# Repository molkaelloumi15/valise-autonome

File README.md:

# 🧳 Valise Autonome

Projet académique (2ᵉ année d'ingénieur, ENSIT, 2024–2025) réalisé en binôme (Molka Elloumi & Fakhri Menjli) : une valise connectée capable de **suivre automatiquement son propriétaire**, d'**éviter les obstacles**, et pilotable via une **application mobile Flutter**.

## 🎯 Fonctionnalités principales

| Fonctionnalité | Description |
|---|---|
| **Suivi autonome** | La valise détecte la position de son propriétaire en temps réel et le suit automatiquement. |
| **Navigation & évitement d'obstacles** | Détection et contournement des obstacles fixes et mobiles à l'aide de capteurs ultrasoniques. |
| **Mode manuel** | Contrôle manuel de la valise depuis l'application mobile. |
| **Notifications** | Alerte envoyée au smartphone en cas de perte de connexion avec la valise. |
| **Autonomie** | Batterie lithium-ion dimensionnée pour au moins 8h d'utilisation continue. |

## 🧠 Principe de fonctionnement

La valise embarque un microcontrôleur **ESP32** qui :
1. Estime la distance au smartphone du propriétaire à partir de la puissance du signal Wi-Fi (RSSI).
2. Mesure en parallèle la distance aux obstacles via un capteur ultrasonique.
3. Compare les deux mesures pour distinguer un vrai obstacle d'un simple éloignement du propriétaire, et ajuste le déplacement des moteurs en conséquence.
4. Expose ces données via un petit serveur web embarqué (mode point d'accès Wi-Fi), interrogé par l'application mobile.

## 🛠️ Stack technique

- **Firmware** : C++ (Arduino), ESP32, capteurs ultrasoniques HC-SR04, moteurs CC à engrenages FIT0564
- **Électronique** : PCB personnalisé conçu sous **KiCad**, prototypage sous **Proteus 8 ISIS**
- **Application mobile** : **Flutter** (architecture MVVM) — authentification, écran d'accueil, suivi en temps réel, réglages
- **Outils** : Arduino IDE, VS Code, KiCad

## 📂 Structure du dépôt

```
.
├── firmware/           # Code embarqué ESP32 (Arduino)
│   └── valise_autonome.ino
├── circuit/             # Conception électronique (KiCad)
│   ├── circuit.kicad_sch / .kicad_pcb / .kicad_pro
│   └── gerbers/          # Fichiers de fabrication (Gerber/drill)
├── mobile-app/          # Application Flutter (code source Dart)
│   ├── lib/
│   │   ├── main.dart
│   │   ├── screens/      # Login, Home, Profil, Réglages
│   │   └── services/     # Authentification, communication ESP32
│   ├── assets/
│   └── pubspec.yaml
└── docs/
    └── Valise_autonome.pdf   # Rapport de projet complet
```

## 📄 Documentation complète

Le rapport de projet complet (cahier des charges, étude de l'existant, architecture, choix techniques, résultats de tests) est disponible dans [`docs/Valise_autonome.pdf`](docs/Valise_autonome.pdf).

## 🚀 Pour reproduire le firmware

1. Ouvrir `firmware/valise_autonome.ino` dans l'Arduino IDE avec le support ESP32 installé.
2. Flasher la carte ESP32.
3. Se connecter au réseau Wi-Fi `Suitcase_AP` créé par la valise.
4. Lancer l'application Flutter (`mobile-app/`) pour piloter et suivre la valise.

---

*Projet réalisé dans le cadre de la formation d'ingénieur à l'ENSEA — Molka Elloumi, [LinkedIn](https://linkedin.com/in/molkaelloumi)*

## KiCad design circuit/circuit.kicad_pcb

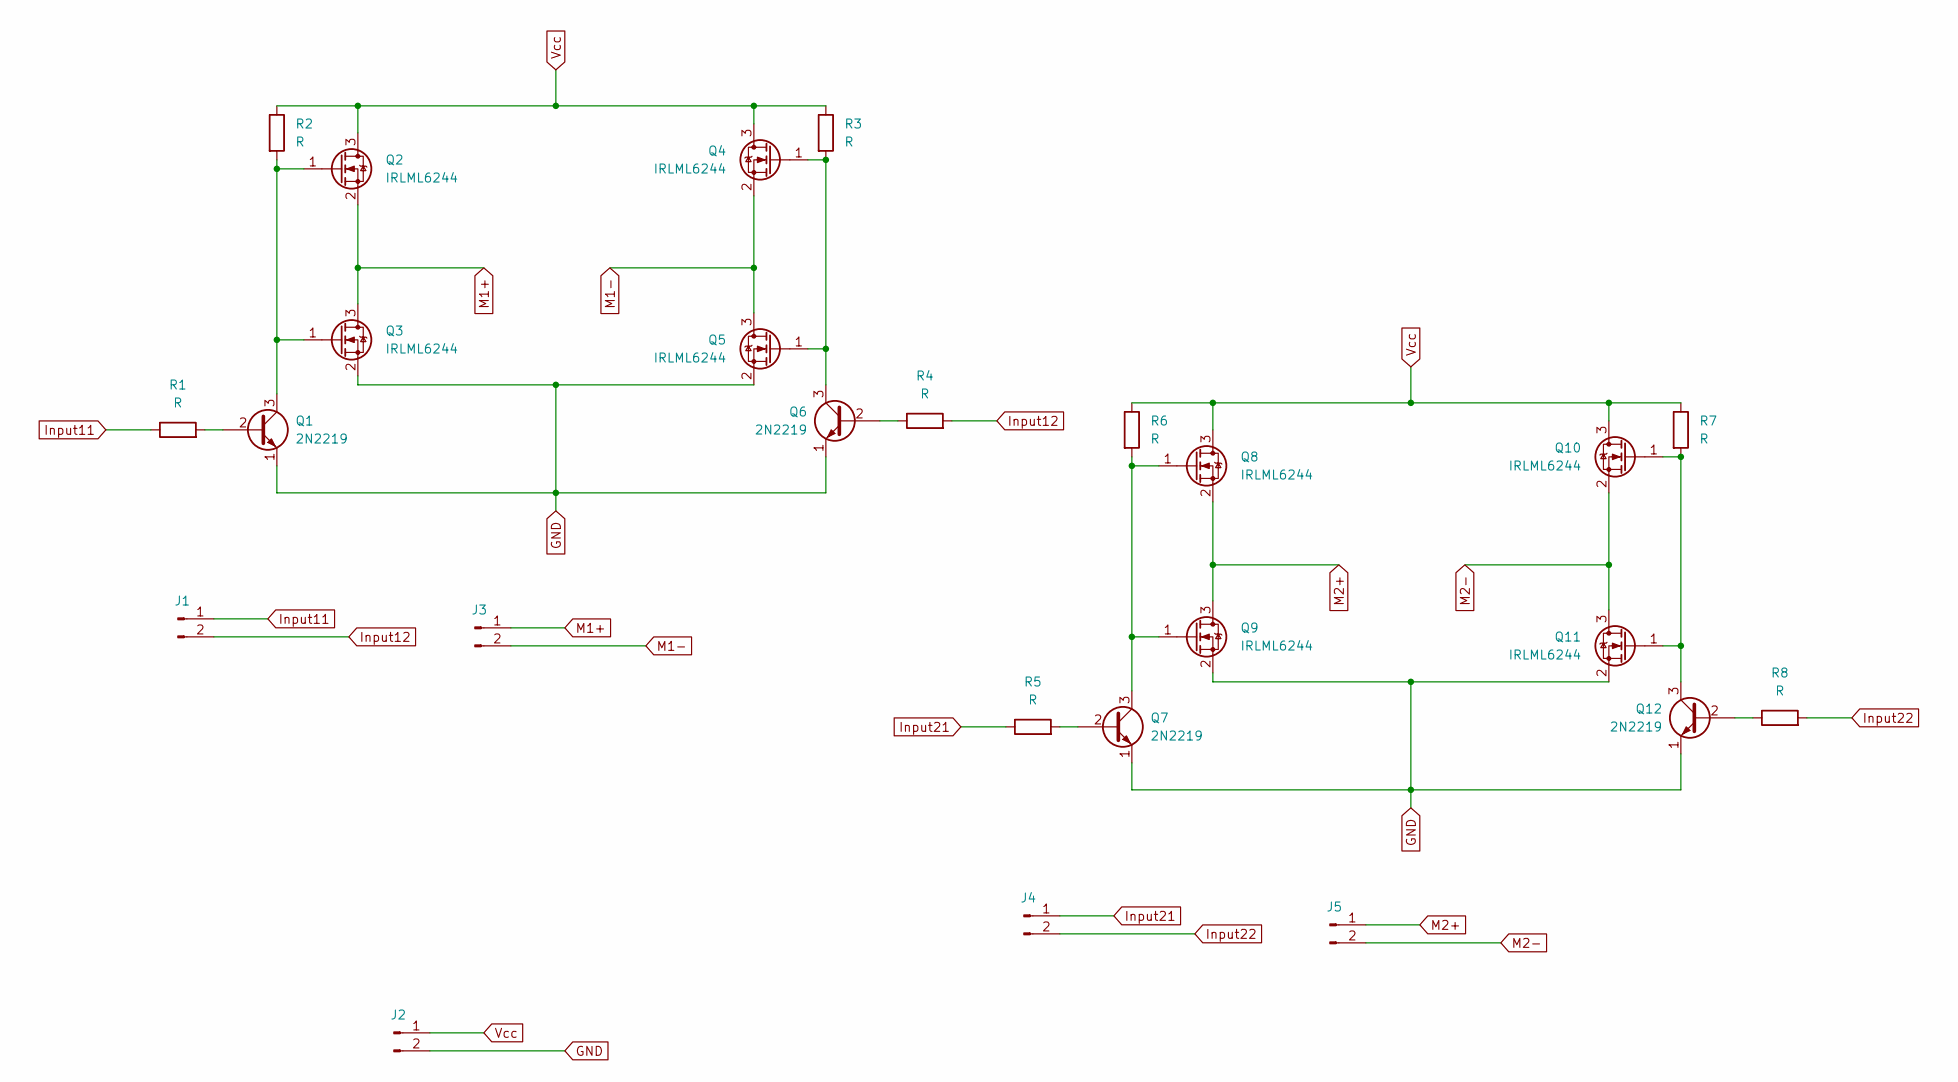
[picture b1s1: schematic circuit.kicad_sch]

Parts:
J1, J2, J3, J4, J5: Conn_01x02_Pin; PinSocket_1x02_P2.54mm_Vertical
Q1, Q6, Q7, Q12: 2N2219; TO-39-3
Q2, Q3, Q4, Q5, Q8, Q9, Q10, Q11: IRLML6244; SOT-23
R1, R2, R3, R4, R5, R6, R7, R8: R; R_Axial_DIN0207_L6.3mm_D2.5mm_P2.54mm_Vertical

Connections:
GND: J2.2, Q1.1 (E), Q3.2 (S), Q5.2 (S), Q6.1 (E), Q7.1 (E), Q9.2 (S), Q11.2 (S), Q12.1 (E)
Input11: J1.1, R1.1
Input12: J1.2, R4.2
Input21: J4.1, R5.1
Input22: J4.2, R8.2
M1+: J3.1, Q2.2 (S), Q3.3 (D)
M1-: J3.2, Q4.2 (S), Q5.3 (D)
M2+: J5.1, Q8.2 (S), Q9.3 (D)
M2-: J5.2, Q10.2 (S), Q11.3 (D)
unnamed: Q1.2 (B), R1.2
unnamed: Q1.3 (C), Q2.1 (G), Q3.1 (G), R2.2
unnamed: Q4.1 (G), Q5.1 (G), Q6.3 (C), R3.2
unnamed: Q6.2 (B), R4.1
unnamed: Q7.2 (B), R5.2
unnamed: Q7.3 (C), Q8.1 (G), Q9.1 (G), R6.2
unnamed: Q10.1 (G), Q11.1 (G), Q12.3 (C), R7.2
unnamed: Q12.2 (B), R8.1
Vcc: J2.1, Q2.3 (D), Q4.3 (D), Q8.3 (D), Q10.3 (D), R2.1, R3.1, R6.1, R7.1

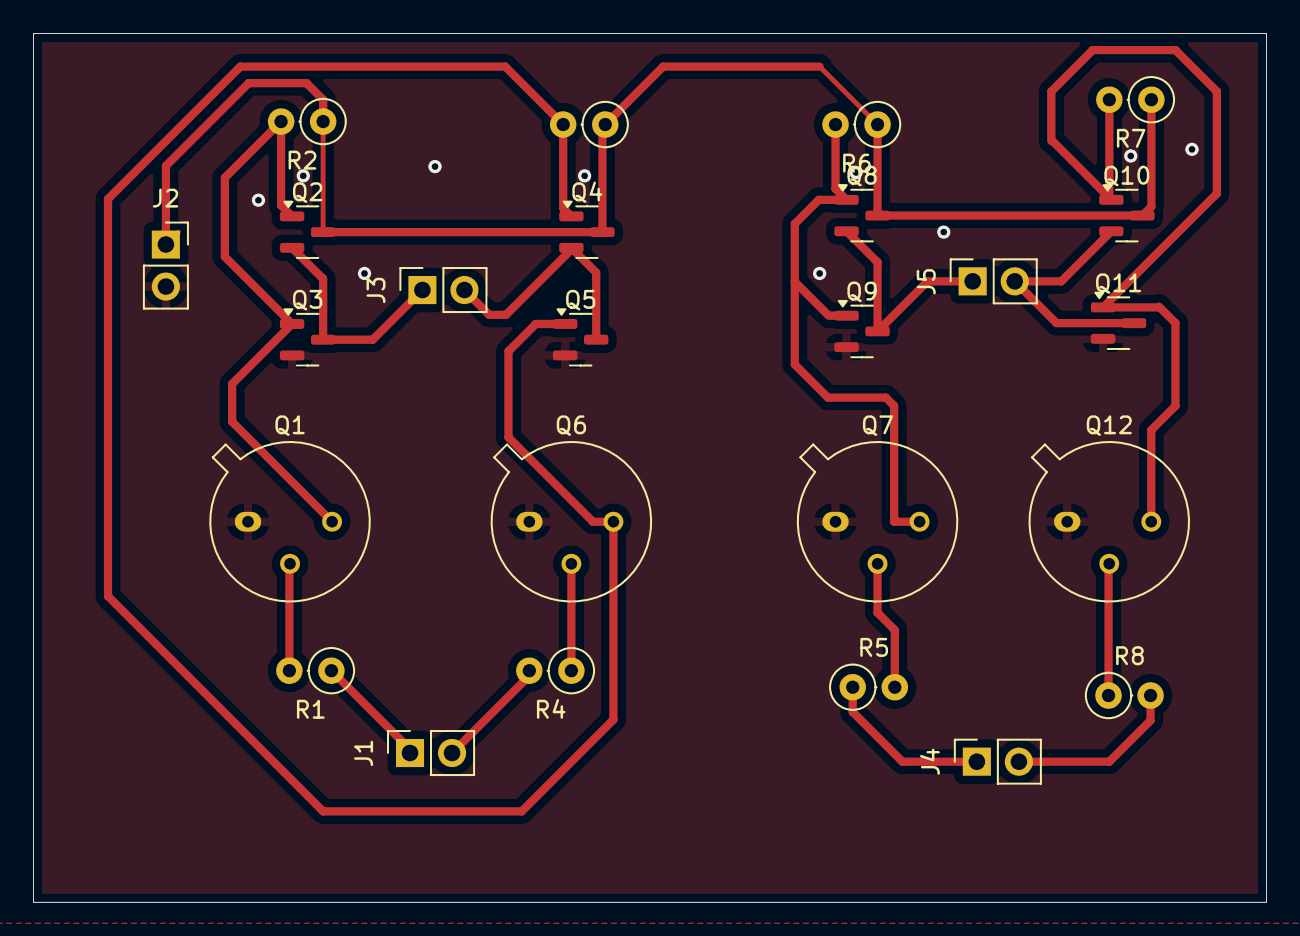
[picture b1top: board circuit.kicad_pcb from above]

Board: 2 copper layers, 74.5 x 52.5 mm, 25 parts (0 on the bottom side), 18 nets.
